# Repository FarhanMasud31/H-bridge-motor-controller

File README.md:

H bridge motor controller.

still learning kicad.
i think by now, i have the basic knowledge of designing a pcb.

https://github.com/yendiDev/h-bridge-dc-motor-controller/tree/main 
for reference, used this design. 

schematic:

front copper layer

back copper layer

3D layout

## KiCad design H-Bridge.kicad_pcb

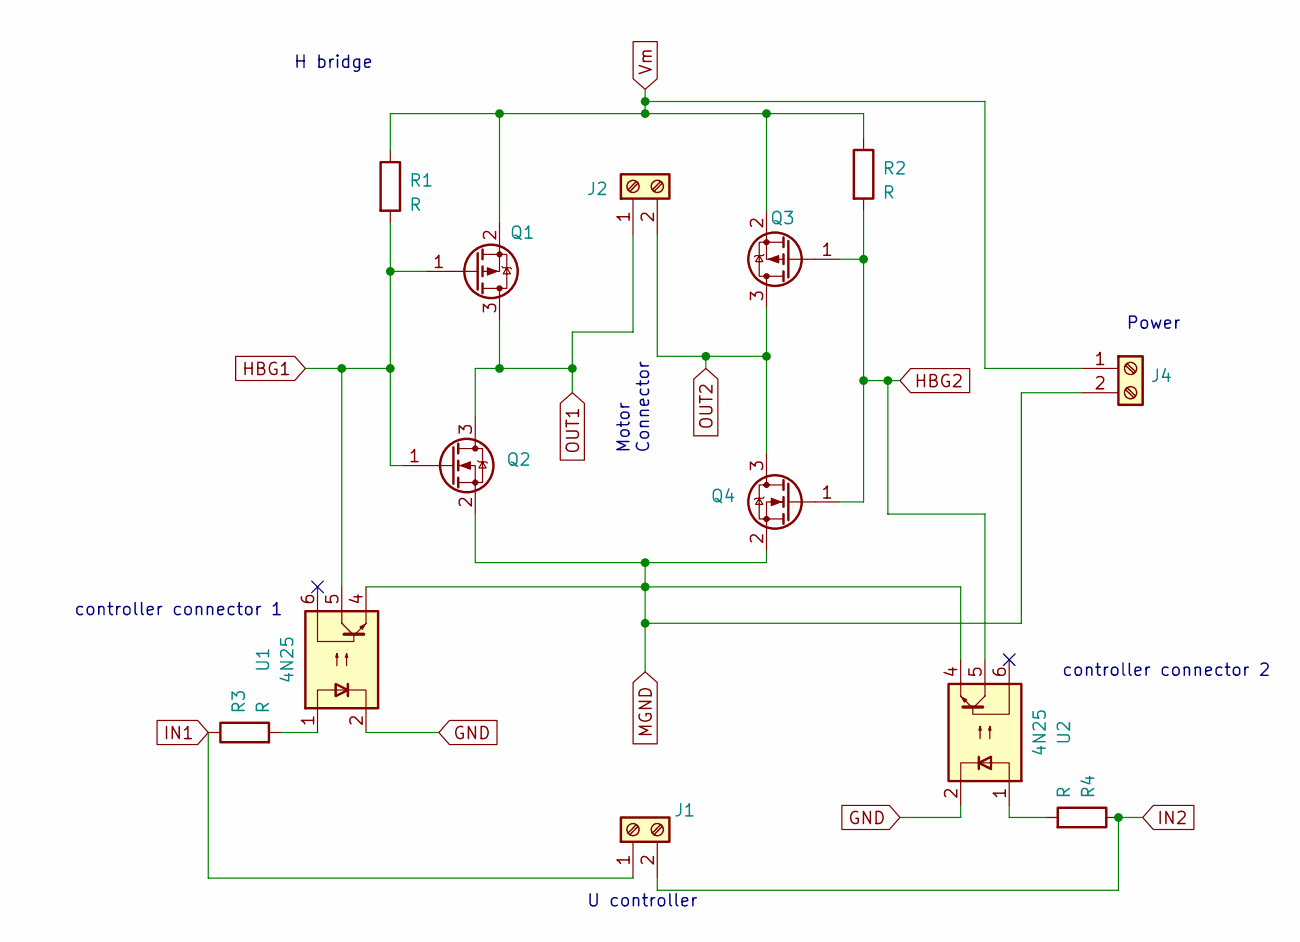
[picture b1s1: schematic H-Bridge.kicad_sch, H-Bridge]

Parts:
J1, J2: Screw_Terminal_01x02; TerminalBlock_Phoenix_MKDS-1,5-2_1x02_P5.00mm_Horizontal
J4: Screw_Terminal_01x02; TerminalBlock_Phoenix_MKDS-1,5-2-5.08_1x02_P5.08mm_Horizont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
Q1, Q3: AO3401A; SOT-23
Q2, Q4: IRLML0030; SOT-23
R1, R2, R3, R4: R; R_Axial_DIN0204_L3.6mm_D1.6mm_P5.08mm_Horizontal
U1, U2: 4N25; DIP-6_W7.62mm

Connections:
GND: U1.2, U2.2; also elsewhere on the board
HBG1: Q1.1 (G), Q2.1 (G), R1.2, U1.5
HBG2: Q3.1 (G), Q4.1 (G), R2.2, U2.5
IN1: J1.1, R3.1
IN2: J1.2, R4.1
MGND: J4.2, Q2.2 (S), Q4.2 (S), U1.4, U2.4
unnamed: R3.2, U1.1
unnamed: R4.2, U2.1
OUT1: J2.1, Q1.3 (D), Q2.3 (D)
OUT2: J2.2, Q3.3 (D), Q4.3 (D)
Vm: J4.1, Q1.2 (S), Q3.2 (S), R1.1, R2.1

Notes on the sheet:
Motor Connector
U controller
controller connector 1
H bridge
Power
controller connector 2

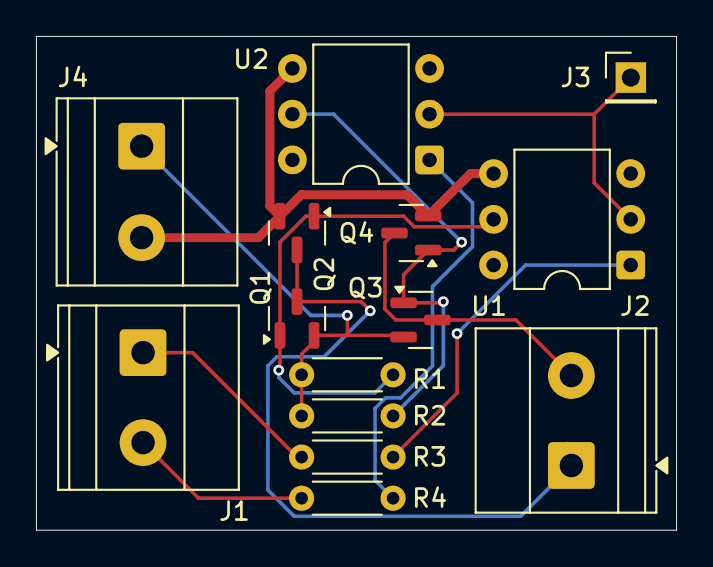
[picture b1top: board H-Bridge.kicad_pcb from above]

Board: 2 copper layers, 35.6 x 27.4 mm, 14 parts (0 on the bottom side), 11 nets.

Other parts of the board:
J3: Conn_01x01_Pin; PinHeader_1x01_P2.54mm_Vertical

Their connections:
GND: J3.1; also elsewhere on the board
